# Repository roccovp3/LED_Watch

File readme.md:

# LED Watch

This is a design for a digital LED watch that fits in a standard watch case. The watch shows the hours on the inner ring of 12 LEDs, and shows the minutes and seconds simultaneously on the outer ring of 60 LEDs. Time is adjustable through a switch in the crown that can be accessed with a paperclip.

## Electronics
A TI MSPM0 microcontroller controls a charlieplexed LED matrix of all 72 LEDs with 9 GPIO pins. Charlieplexing was chosen as it would otherwise take 17 GPIO pins to control the matrix with the more traditional wiring method. Timing is done via an external TCXO to minimize drift.

I chose the MSPM0 because I already had the development kit, and I was familiar with the device. With a project this simple, the MSPM0's low power consumption, minimal external component requirements, and integrated voltage regulator made it an adequate choice. In a future revision I could even opt for one of its smaller packages.

As for the LEDs, they are all 0402 packages with the inner ones being a yellow-green and the outer ones being a more solid green. In hindsight I would have opted for the green LEDs for everything because they have better diffusion and brightness and their package was much easier to solder. I knew when assembling that choosing the right current limiting resistors to set the maximum brightness was going to be trial and error, but I was surprised at just how much resistance I was able to put on the GPIO pins while keeping the LEDs more than bright enough for a well lit room. Each GPIO pin has 2kΩ on it, meaning the LEDs see 4kΩ each. With a 2.0V drop this means the maximum current through any given LED is about (3.3-2.0)/4000 = 300uA. Since the way the software is written means exactly one LED is on at all times, 300uA is the entire contribution of system current from the LEDs.

Powering this device required careful thought. I wanted to optimize for runtime given the space constraints, and it was hard to beat a coin-cell for this purpose. I chose the CR2032 both because it and it's holder fit nicely on the back of the PCB as well as their wide availability. The CR2450 was a tempting alternative, but I opted for the lower capacity (and smaller) CR2032 because of how easy they are to find. Initially, I thought a voltage regulator was necessary for this project which would have hurt battery life and required more components to be packed onto the PCB. Luckily, the MSPM0 has a wide input voltage range of 1.62 to 3.6V, making the CR2032 suitable to power the device throughout its entire lifespan (CR2032 batteries start at about 3.0V and die at about 1.8V).

## Physical Design
The 29.6mm PCB diameter was chosen to fit in a standard watch case. The watch case I used for this project claimed to fit a 28.5 to 29.2mm watch dial. Other research indicated that 29.5mm was the typical maximum dial size for the movement designed to fit in this case. The 29.6mm diameter allowed me to slowly sand away the edge of the PCB until the fit in the case was perfectly snug. The final diameter after sanding ended up being about 29.3mm. I was also careful to leave myself some space to sand by not routing traces near the board edge.

I chose a low-profile momentary switch on the back of the board to serve as an input for setting the time. This switch aligns well with the crown, making it accessible even when the watch is fully assembled. A challenge I would like to tackle in a future revision is attaching the crown to the switch so that it remains attached to the watch at all times and serves as a button itself. As of now, the crown completely unscrews from the watch making it easy to lose.

6 pads are exposed for the signals required to program the microcontroller. This programming method works, but in a future revision it would be nice to find a small connector so I don't have to solder wires to the board every time I think of a way to improve the firmware.

## Firmware
The firmware for the watch is minimal. The TCXO causes an interrupt every 32kHz. On every interrupt a master 15-bit (32768 possible values) counter is incremented. Every time the counter rolls over, the seconds LED updates as well as the minutes and hours if necessary. Between rollovers, the master counter serves as a way to define which of the three LEDs is on in the matrix. Charlieplexing relies on persistence of vision because only one LED can be on at one time. To do this, I look at the lower 7 bits (128 values) of the counter and whether those lower bits are in one of three ranges dictates which of the three possible LEDs is on (in fact, to compensate for my hour LEDs being dimmer, I give them more on-time by making their share of these 128 values larger than the minute/second LEDs). I choose 7 bits because choosing a larger number slows down the switching between the three LEDs enough to make flickering visible on my phone camera. On a 32kHz clock, to cycle through all 128 values takes about 3.9ms. A camera recording at 120 FPS captures a frame every 8.3ms. Becuase our period is less than the camera's, we avoid the flicker by guaranteeing all three LEDs are on at some point during each frame's exposure.

The only other part of the firmware is input management. The crown button allows the user to set the time. Pressing the button for less than a second will increment the hour, minute, or second. Pressing the button for more than a second will cycle between setting the hour, minute, or second.

When the microcontroller is not processing interrupts related to either keeping the time or setting the time, it is in standby mode to minimize power consumption.

## Images

KiCad 3D Model

Partially assembled. Getting the inner LEDs down was tricky as unlike the package for the outer ones, the pads are only exposed on the bottom and not on the sides.

Paritally assembled for a test fit in the case. I was surprise at how well it fit first try. The components had ample clearance between them and the glass. The PCB rests on a lip that provides this spacing.

Back of the case where the battery holder and switch can be seen. Getting a watch case with a clear back was definitely the correct decision :-)

Programming with an MSPM0 development board. These wires are pretty annoying, but they work!

Size comparison with my watch.

Fully assembled. It's 1:12:27!

Fully assembled (back). Battery installed.

## Videos
Videos with the watch fully working are in the img/ directory. GitHub does not currently support embedding videos over 10MB in readmes.

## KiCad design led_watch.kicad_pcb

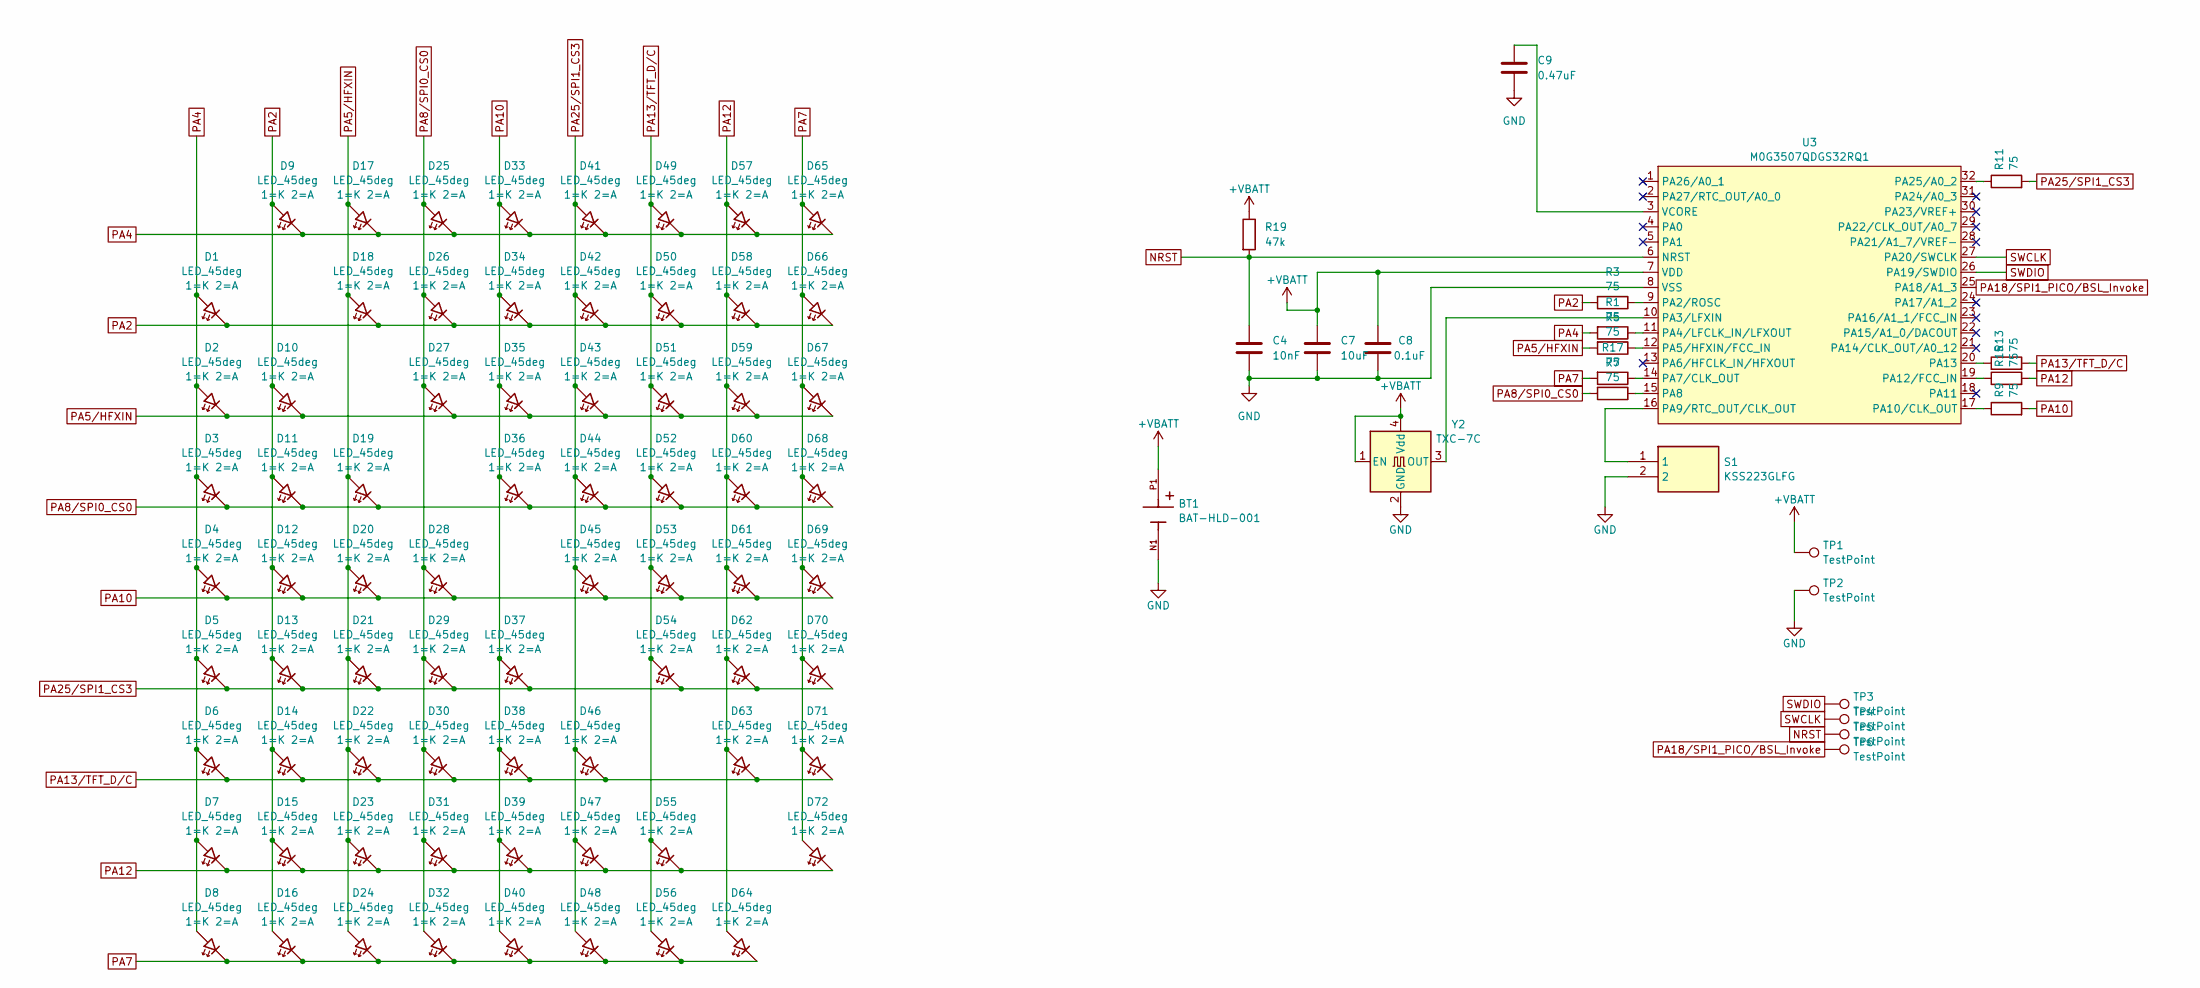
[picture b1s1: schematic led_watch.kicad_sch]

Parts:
BT1: BAT-HLD-001; BAT_BAT-HLD-001; PARTREV C
C4: 10nF; C_0805_2012Metric_Pad1.18x1.45mm_HandSolder
C7: 10uF; C_0805_2012Metric_Pad1.18x1.45mm_HandSolder
C8: 0.1uF; C_0805_2012Metric_Pad1.18x1.45mm_HandSolder
C9: 0.47uF; C_0805_2012Metric_Pad1.18x1.45mm_HandSolder
D1, D2, D3, D4, D5, D6, D7, D8, D9, D10, D11, D12, D13, D14, D15, D16, D17, D18, D19, D20, D21, D22, D23, D24, D25, D26, D27, D28, D29, D30, D31, D32, D33, D34, D35, D36, D37, D38, D39, D40, D41, D42, D43, D44, D45, D46, D47, D48, D49, D50, D51, D52, D53, D54, D55, D56, D57, D58, D59, D60, D61, D62, D63, D64, D65, D66, D67, D68, D69, D70, D71, D72: LED_45deg; LED_0402_1005Metric_Pad0.77x0.64mm_HandSolder
R1, R3, R5, R7, R9, R11, R13, R15, R17: 75; R_0805_2012Metric_Pad1.20x1.40mm_HandSolder
R19: 47k; R_0805_2012Metric_Pad1.20x1.40mm_HandSolder
S1: KSS223GLFG; Mouser Part Number 611-KSS223GLFG
TP1, TP2, TP3, TP4, TP5, TP6: TestPoint; TestPoint_Pad_D1.0mm
U3: M0G3507QDGS32RQ1; generic_VSSOP_0.5mm
Y2: TXC-7C; Oscillator_SMD_Abracon_ASE-4Pin_3.2x2.5mm_HandSoldering

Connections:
+VBATT: BT1.P1, BT1.P2, C7.1, C8.1, R19.1, TP1.1, U3.7 (VDD), Y2.1 (EN), Y2.4 (Vdd)
GND: BT1.N1, C4.2, C7.2, C8.2, C9.2, S1.2, TP2.1, U3.8 (VSS), Y2.2 (GND)
NRST: C4.1, R19.2, TP5.1, U3.6 (NRST)
unnamed: R3.1, U3.9 (PA2/ROSC)
unnamed: U3.10 (PA3/LFXIN), Y2.3 (OUT)
unnamed: R1.1, U3.11 (PA4/LFCLK_IN/LFXOUT)
unnamed: R5.1, U3.12 (PA5/HFXIN/FCC_IN)
unnamed: R17.1, U3.14 (PA7/CLK_OUT)
unnamed: R7.1, U3.15 (PA8)
unnamed: S1.1, U3.16 (PA9/RTC_OUT/CLK_OUT)
unnamed: R9.1, U3.17 (PA10/CLK_OUT)
unnamed: R15.1, U3.19 (PA12/FCC_IN)
unnamed: R13.1, U3.20 (PA13)
unnamed: R11.1, U3.32 (PA25/A0_2)
unnamed: C9.1, U3.3 (VCORE)
PA2: D1.1 (K), D9.2 (A), D10.2 (A), D11.2 (A), D12.2 (A), D13.2 (A), D14.2 (A), D15.2 (A), D16.2 (A), D18.1 (K), D26.1 (K), D34.1 (K), D42.1 (K), D50.1 (K), D58.1 (K), D66.1 (K), R3.2
PA4: D1.2 (A), D2.2 (A), D3.2 (A), D4.2 (A), D5.2 (A), D6.2 (A), D7.2 (A), D8.2 (A), D9.1 (K), D17.1 (K), D25.1 (K), D33.1 (K), D41.1 (K), D49.1 (K), D57.1 (K), D65.1 (K), R1.2
PA5/HFXIN: D2.1 (K), D10.1 (K), D17.2 (A), D18.2 (A), D19.2 (A), D20.2 (A), D21.2 (A), D22.2 (A), D23.2 (A), D24.2 (A), D27.1 (K), D35.1 (K), D43.1 (K), D51.1 (K), D59.1 (K), D67.1 (K), R5.2
PA7: D8.1 (K), D16.1 (K), D24.1 (K), D32.1 (K), D40.1 (K), D48.1 (K), D56.1 (K), D64.1 (K), D65.2 (A), D66.2 (A), D67.2 (A), D68.2 (A), D69.2 (A), D70.2 (A), D71.2 (A), D72.2 (A), R17.2
PA8/SPI0_CS0: D3.1 (K), D11.1 (K), D19.1 (K), D25.2 (A), D26.2 (A), D27.2 (A), D28.2 (A), D29.2 (A), D30.2 (A), D31.2 (A), D32.2 (A), D36.1 (K), D44.1 (K), D52.1 (K), D60.1 (K), D68.1 (K), R7.2
PA10: D4.1 (K), D12.1 (K), D20.1 (K), D28.1 (K), D33.2 (A), D34.2 (A), D35.2 (A), D36.2 (A), D37.2 (A), D38.2 (A), D39.2 (A), D40.2 (A), D45.1 (K), D53.1 (K), D61.1 (K), D69.1 (K), R9.2
PA12: D7.1 (K), D15.1 (K), D23.1 (K), D31.1 (K), D39.1 (K), D47.1 (K), D55.1 (K), D57.2 (A), D58.2 (A), D59.2 (A), D60.2 (A), D61.2 (A), D62.2 (A), D63.2 (A), D64.2 (A), D72.1 (K), R15.2
PA13/TFT_D/C: D6.1 (K), D14.1 (K), D22.1 (K), D30.1 (K), D38.1 (K), D46.1 (K), D49.2 (A), D50.2 (A), D51.2 (A), D52.2 (A), D53.2 (A), D54.2 (A), D55.2 (A), D56.2 (A), D63.1 (K), D71.1 (K), R13.2
PA18/SPI1_PICO/BSL_Invoke: TP6.1, U3.25 (PA18/A1_3)
PA25/SPI1_CS3: D5.1 (K), D13.1 (K), D21.1 (K), D29.1 (K), D37.1 (K), D41.2 (A), D42.2 (A), D43.2 (A), D44.2 (A), D45.2 (A), D46.2 (A), D47.2 (A), D48.2 (A), D54.1 (K), D62.1 (K), D70.1 (K), R11.2
SWCLK: TP4.1, U3.27 (PA20/SWCLK)
SWDIO: TP3.1, U3.26 (PA19/SWDIO)

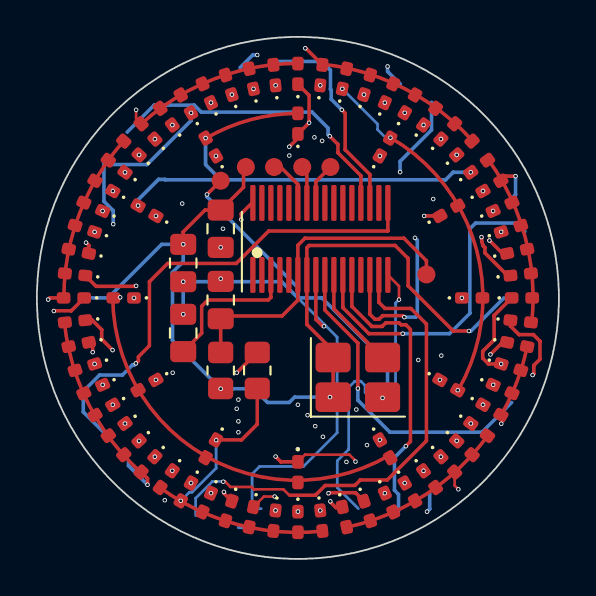
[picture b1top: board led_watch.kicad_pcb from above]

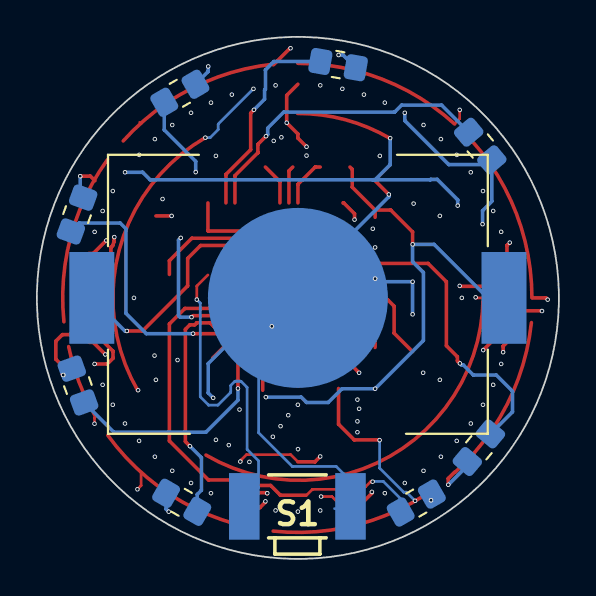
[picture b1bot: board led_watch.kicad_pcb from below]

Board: 4 copper layers, 29.0 x 29.0 mm, 96 parts (10 on the bottom side), 27 nets.

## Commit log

2025-10-11 readme
2025-10-16 4 layers, removed regulator
2025-10-17 remove half of resistors, routing cleanup
2025-10-18 rounded tracks
2025-10-23 add button
2025-11-08 functional sw with TCXO and hour LEDs moving at 1Hz
2025-11-08 clean up root repo dir
2025-11-08 remove TI readmes
2025-11-10 able to set time, hours min and seconds all working at once
2025-11-10 fix off by 15 error, add ability to adjust seconds
2025-11-10 cleanup hw dir, move readme
2025-11-10 add BOM
2025-11-19 add MSP 3D model
2025-11-29 Starting changes to sysconfig to make PA3/LFXIN a wakeup source and putting the MSPM0 in standby mode which draws far less current than sleep mode. Have to play around with the registers to get the i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
2025-11-29 enable FastWake on TXCO pin (PA3) in hopes of being able to put MSPM0 in standby (lower power state than sleep)
2025-11-29 add media
2025-11-29 Add writeup
2025-11-30 change power policy to put watch in standby
